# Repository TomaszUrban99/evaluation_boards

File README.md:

# evaluation_boards
A GitHub repository featuring example projects for various evaluation and development boards.

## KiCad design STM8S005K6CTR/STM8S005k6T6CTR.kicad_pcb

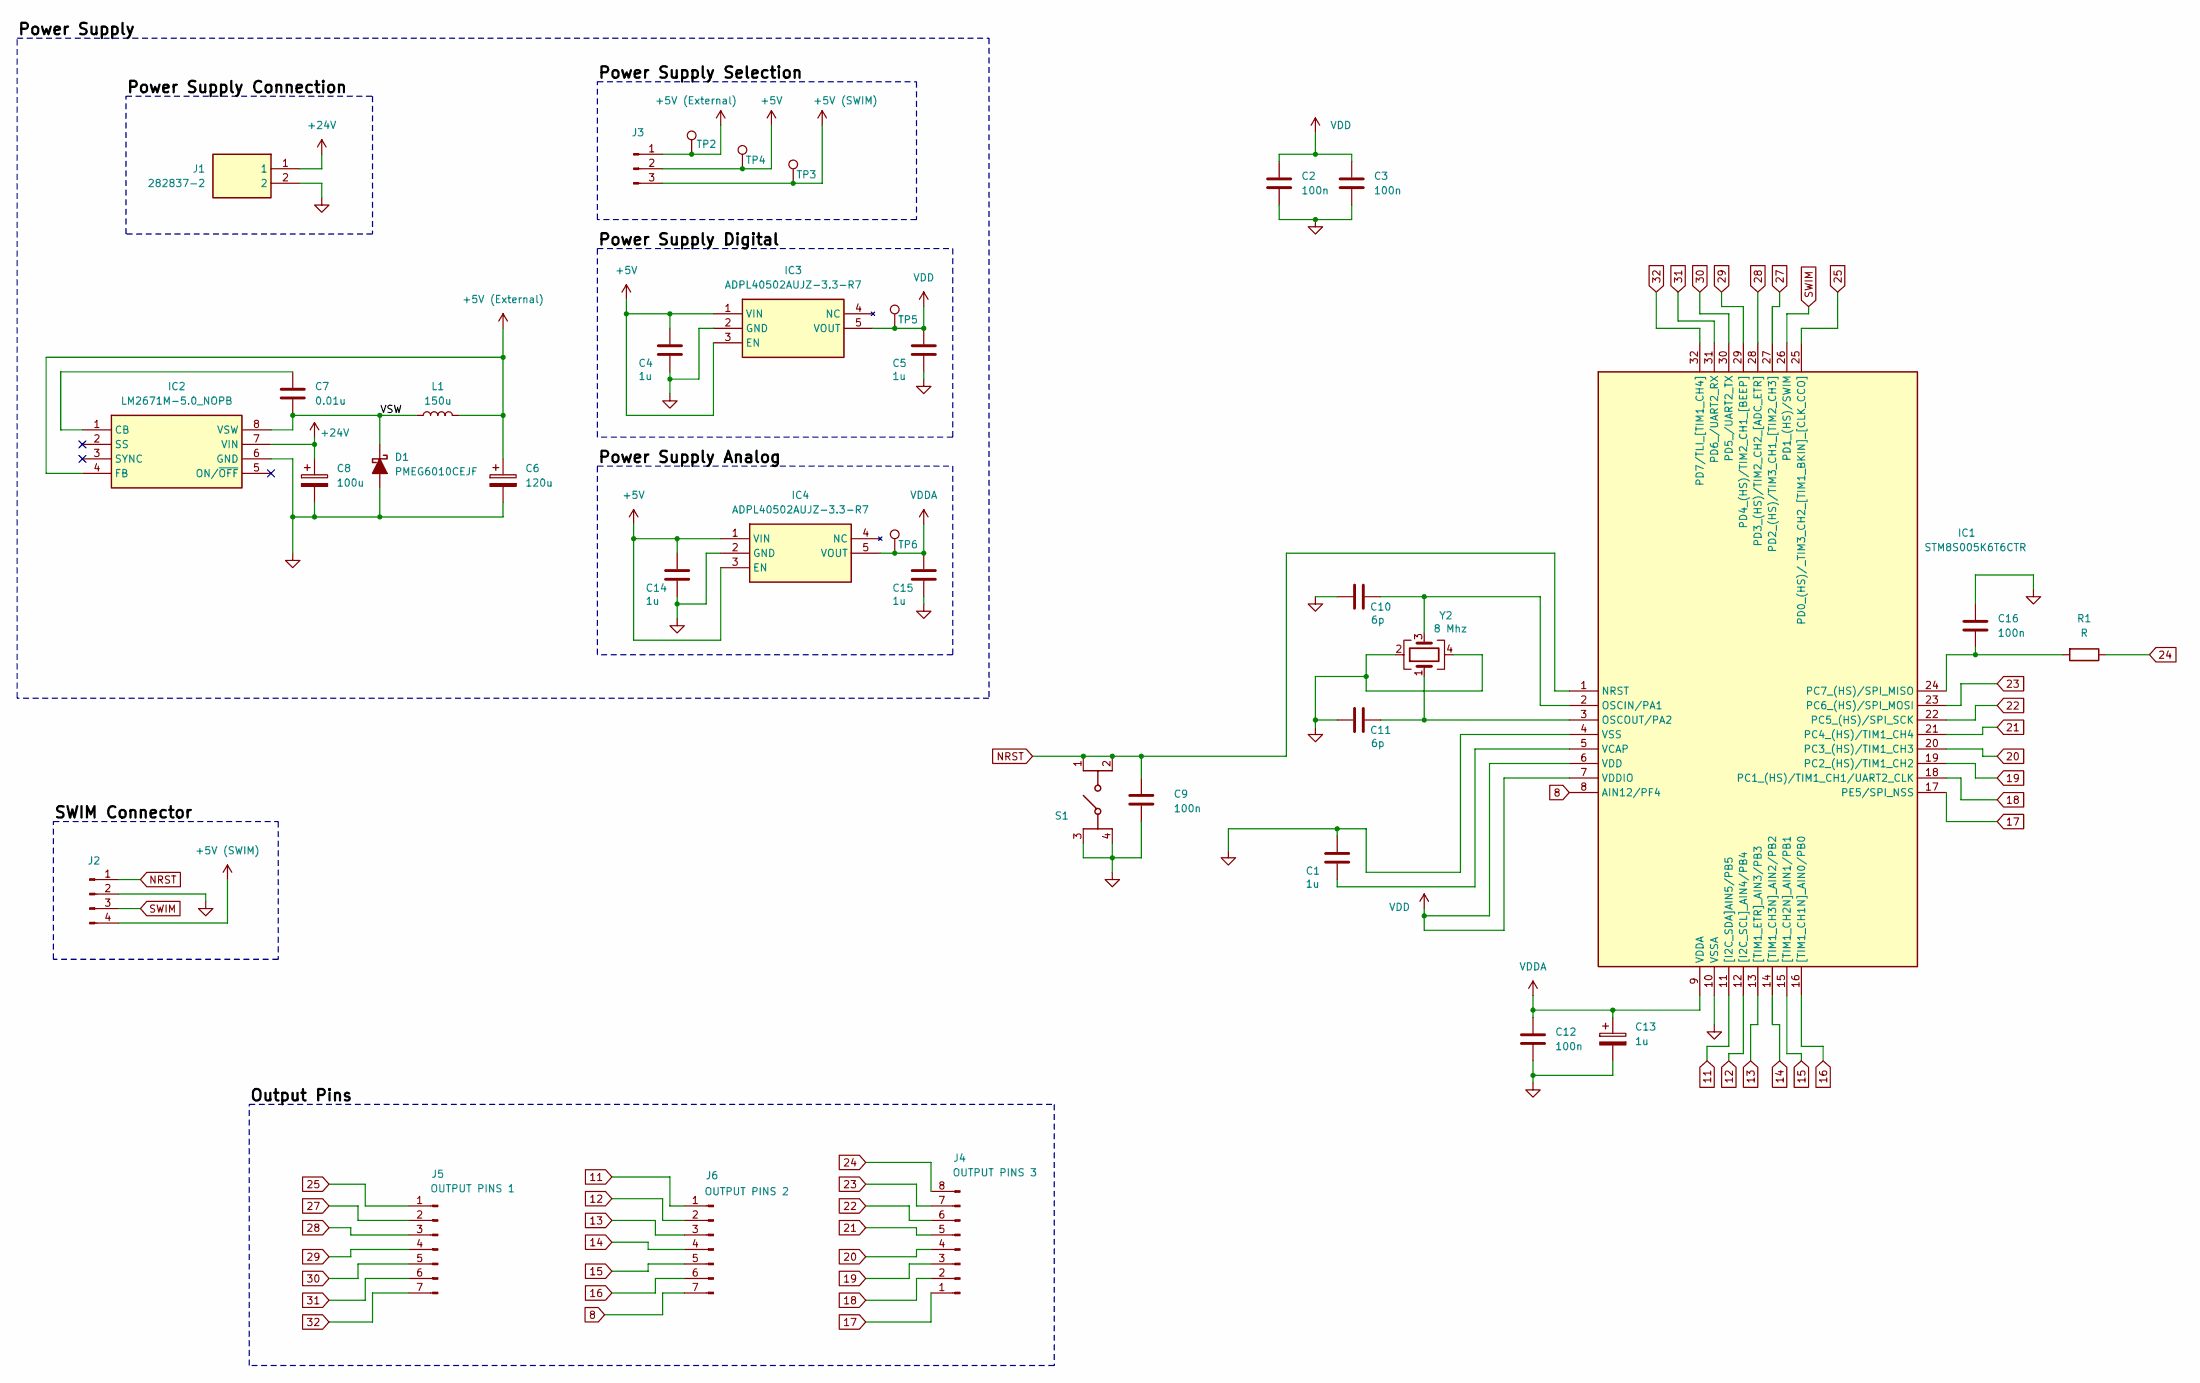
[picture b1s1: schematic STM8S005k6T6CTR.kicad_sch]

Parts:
C1, C4, C5, C14, C15: 1u; C_0603_1608Metric
C2, C3, C9, C12, C16: 100n; C_0603_1608Metric
C6: 120u; CP_Radial_D10.0mm_P5.00mm
C7: 0.01u; C_0603_1608Metric
C8: 100u; CP_Radial_D10.0mm_P5.00mm
C10, C11: 6p; C_0402_1005Metric
C13: 1u; C_1210_3225Metric
D1: PMEG6010CEJF; D_SOD-323F
IC1: STM8S005K6T6CTR; QFP80P900X900X160-32N; Mouser Part Number 511-STM8S005K6T6CTR
IC2: LM2671M-5.0_NOPB; SOIC127P600X175-8N; Mouser Part Number 926-LM2671M-5.0/NOPB
IC3, IC4: ADPL40502AUJZ-3.3-R7; SOT95P280X100-5N; Mouser Part Number 584-ADPL40502AUJZ33R
J1: 282837-2; 2828372; Mouser Part Number 571-2828372
J2: Conn_01x04_Pin; PinHeader_1x04_P2.54mm_Vertical
J3: Conn_01x03_Pin; PinHeader_1x03_P2.54mm_Vertical
J4: Conn_01x08_Pin; PinSocket_1x08_P2.54mm_Vertical
J5, J6: Conn_01x07_Pin; PinSocket_1x07_P2.54mm_Vertical
L1: 150u; WE-TPC_1028_103892
R1: R
S1: PTS647SK70SMTR2N_LFS; PTS647SK70SMTR2NLFS; Manufacturer_Part_Number PTS647SK70SMTR2N LFS
TP2, TP3, TP4, TP5, TP6: TestPoint; TestPoint_Pad_D1.5mm
Y2: 8 Mhz; ECS80833B2QCVYTR3

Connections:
8: IC1.8 (AIN12/PF4), J6.7
11: IC1.11 ([I2C_SDA]AIN5/PB5), J6.1
12: IC1.12 ([I2C_SCL]_AIN4/PB4), J6.2
13: IC1.13 ([TIM1_ETR]_AIN3/PB3), J6.3
14: IC1.14 ([TIM1_CH3N]_AIN2/PB2), J6.4
15: IC1.15 ([TIM1_CH2N]_AIN1/PB1), J6.5
16: IC1.16 ([TIM1_CH1N]_AIN0/PB0), J6.6
17: IC1.17 (PE5/SPI_NSS), J4.1
18: IC1.18 (PC1_(HS)/TIM1_CH1/UART2_CLK), J4.2
19: IC1.19 (PC2_(HS)/TIM1_CH2), J4.3
20: IC1.20 (PC3_(HS)/TIM1_CH3), J4.4
21: IC1.21 (PC4_(HS)/TIM1_CH4), J4.5
22: IC1.22 (PC5_(HS)/SPI_SCK), J4.6
23: IC1.23 (PC6_(HS)/SPI_MOSI), J4.7
24: J4.8, R1.1
25: IC1.25 (PD0_(HS)/_TIM3_CH2_[TIM1_BKIN]_[CLK_CCO]), J5.1
27: IC1.27 (PD2_(HS)/TIM3_CH1_[TIM2_CH3]), J5.2
28: IC1.28 (PD3_(HS)/TIM2_CH2_[ADC_ETR]), J5.3
29: IC1.29 (PD4_(HS)/TIM2_CH1_[BEEP]), J5.4
30: IC1.30 (PD5_/UART2_TX), J5.5
31: IC1.31 (PD6_/UART2_RX), J5.6
32: IC1.32 (PD7/TLI_[TIM1_CH4]), J5.7
+5V: C4.1, C14.1, IC3.1 (VIN), IC3.3 (EN), IC4.1 (VIN), IC4.3 (EN), J3.2, TP4.1
+5V (External): C6.1, IC2.4 (FB), J3.1, L1.2, TP2.1
+5V (SWIM): J2.4, J3.3, TP3.1
+24V: C8.1, IC2.7 (VIN), J1.1
GND: C1.1, C2.2, C3.2, C4.2, C5.2, C6.2, C8.2, C9.2, C10.2, C11.2, C12.2, C13.2, C14.2, C15.2, C16.1, D1.2 (A), IC1.4 (VSS), IC1.10 (VSSA), IC2.6 (GND), IC3.2 (GND), IC4.2 (GND), J1.2, J2.2, S1.3 (COM_1), S1.4 (COM_2), Y2.2, Y2.4
NRST: C9.1, IC1.1 (NRST), J2.1, S1.1 (NO_1), S1.2 (NO_2)
unnamed: C7.1, D1.1 (K), IC2.8 (VSW), L1.1
unnamed: C10.1, IC1.2 (OSCIN/PA1), Y2.3
unnamed: C11.1, IC1.3 (OSCOUT/PA2), Y2.1
unnamed: C16.2, IC1.24 (PC7_(HS)/SPI_MISO), R1.2
unnamed: C1.2, IC1.5 (VCAP)
unnamed: C7.2, IC2.1 (CB)
SWIM: IC1.26 (PD1_(HS)/SWIM), J2.3
VDD: C2.1, C3.1, C5.1, IC1.6 (VDD), IC1.7 (VDDIO), IC3.5 (VOUT), TP5.1
VDDA: C12.1, C13.1, C15.1, IC1.9 (VDDA), IC4.5 (VOUT), TP6.1

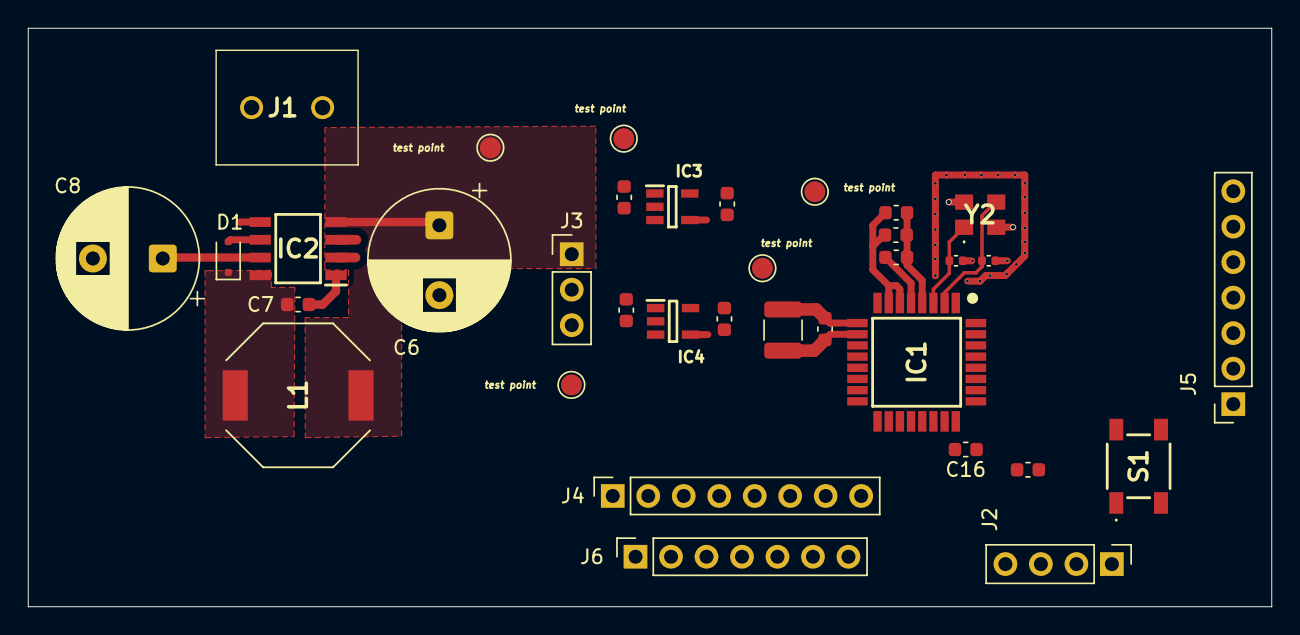
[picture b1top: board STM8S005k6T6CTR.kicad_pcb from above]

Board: 2 copper layers, 89.0 x 41.4 mm, 35 parts (0 on the bottom side), 36 nets.

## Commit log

2025-09-05 [STM8S005K6t6CTR] Added 8-bit uC. Added L6981 voltage switch regulator with component's values.
2025-09-11 [STM8S005K6T6CTR] Calculations: calculated values of components for switching voltage regulator - TI LM2671. Board scheme: Added switching voltage regulator with additional components. Assigned footp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
2025-09-11 [STM8S005K6T6CTR] Board scheme: Added Power Supply Selecection pins. Added SWIM connector.
2025-09-14 [STM8S005K6T6CTR] Calculations: calculated crystal components. Board scheme: Added crystal to scheme (with footprint). Added part of output pins.
2025-09-14 [STM8S005K6T6CTR] Board scheme: assigned footprints to decoupling capacitors and VCAP capacitor.
2025-09-21 [STM8S005K6T6CTR] Board scheme: Improvements
2025-09-25 [STM8S005K6T6CTR] Board scheme: Footprints layout. Crystal routing.
